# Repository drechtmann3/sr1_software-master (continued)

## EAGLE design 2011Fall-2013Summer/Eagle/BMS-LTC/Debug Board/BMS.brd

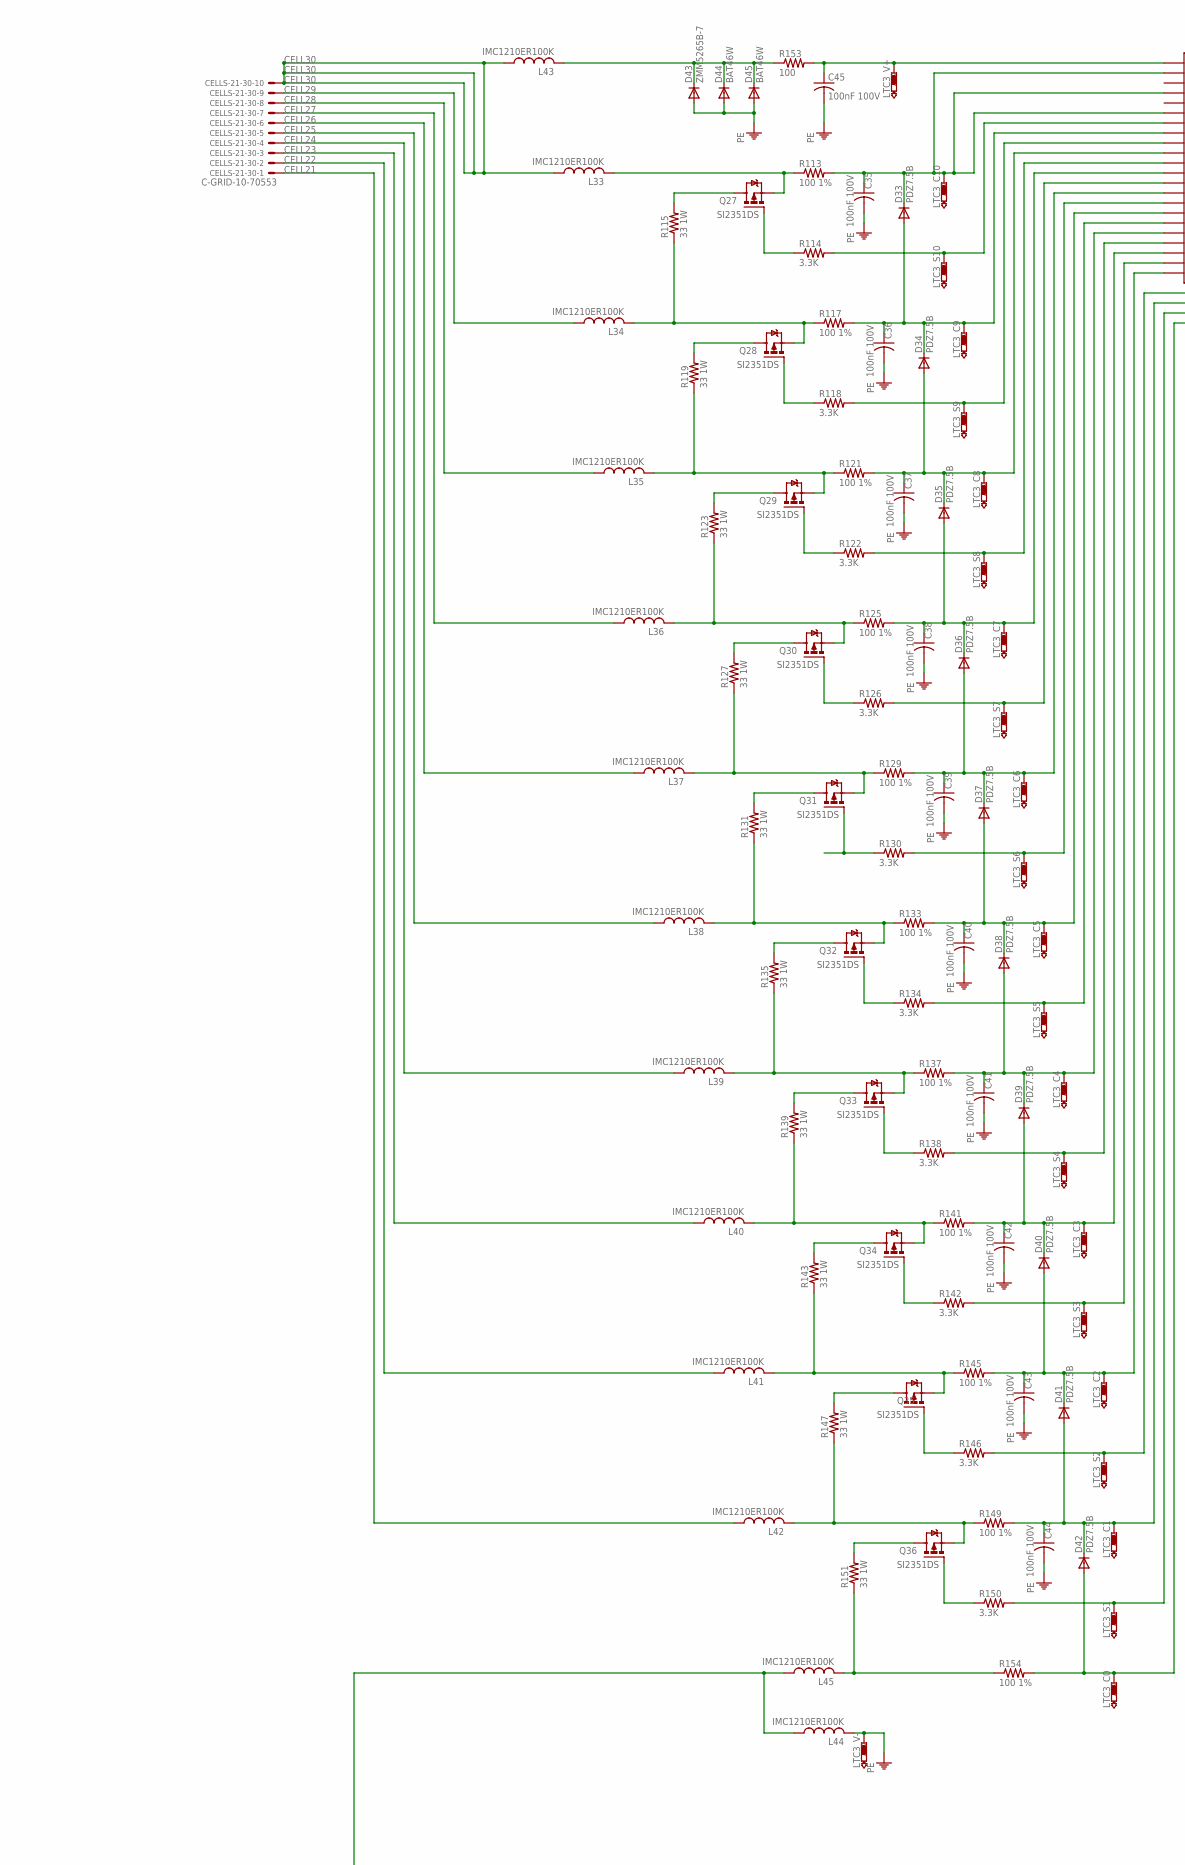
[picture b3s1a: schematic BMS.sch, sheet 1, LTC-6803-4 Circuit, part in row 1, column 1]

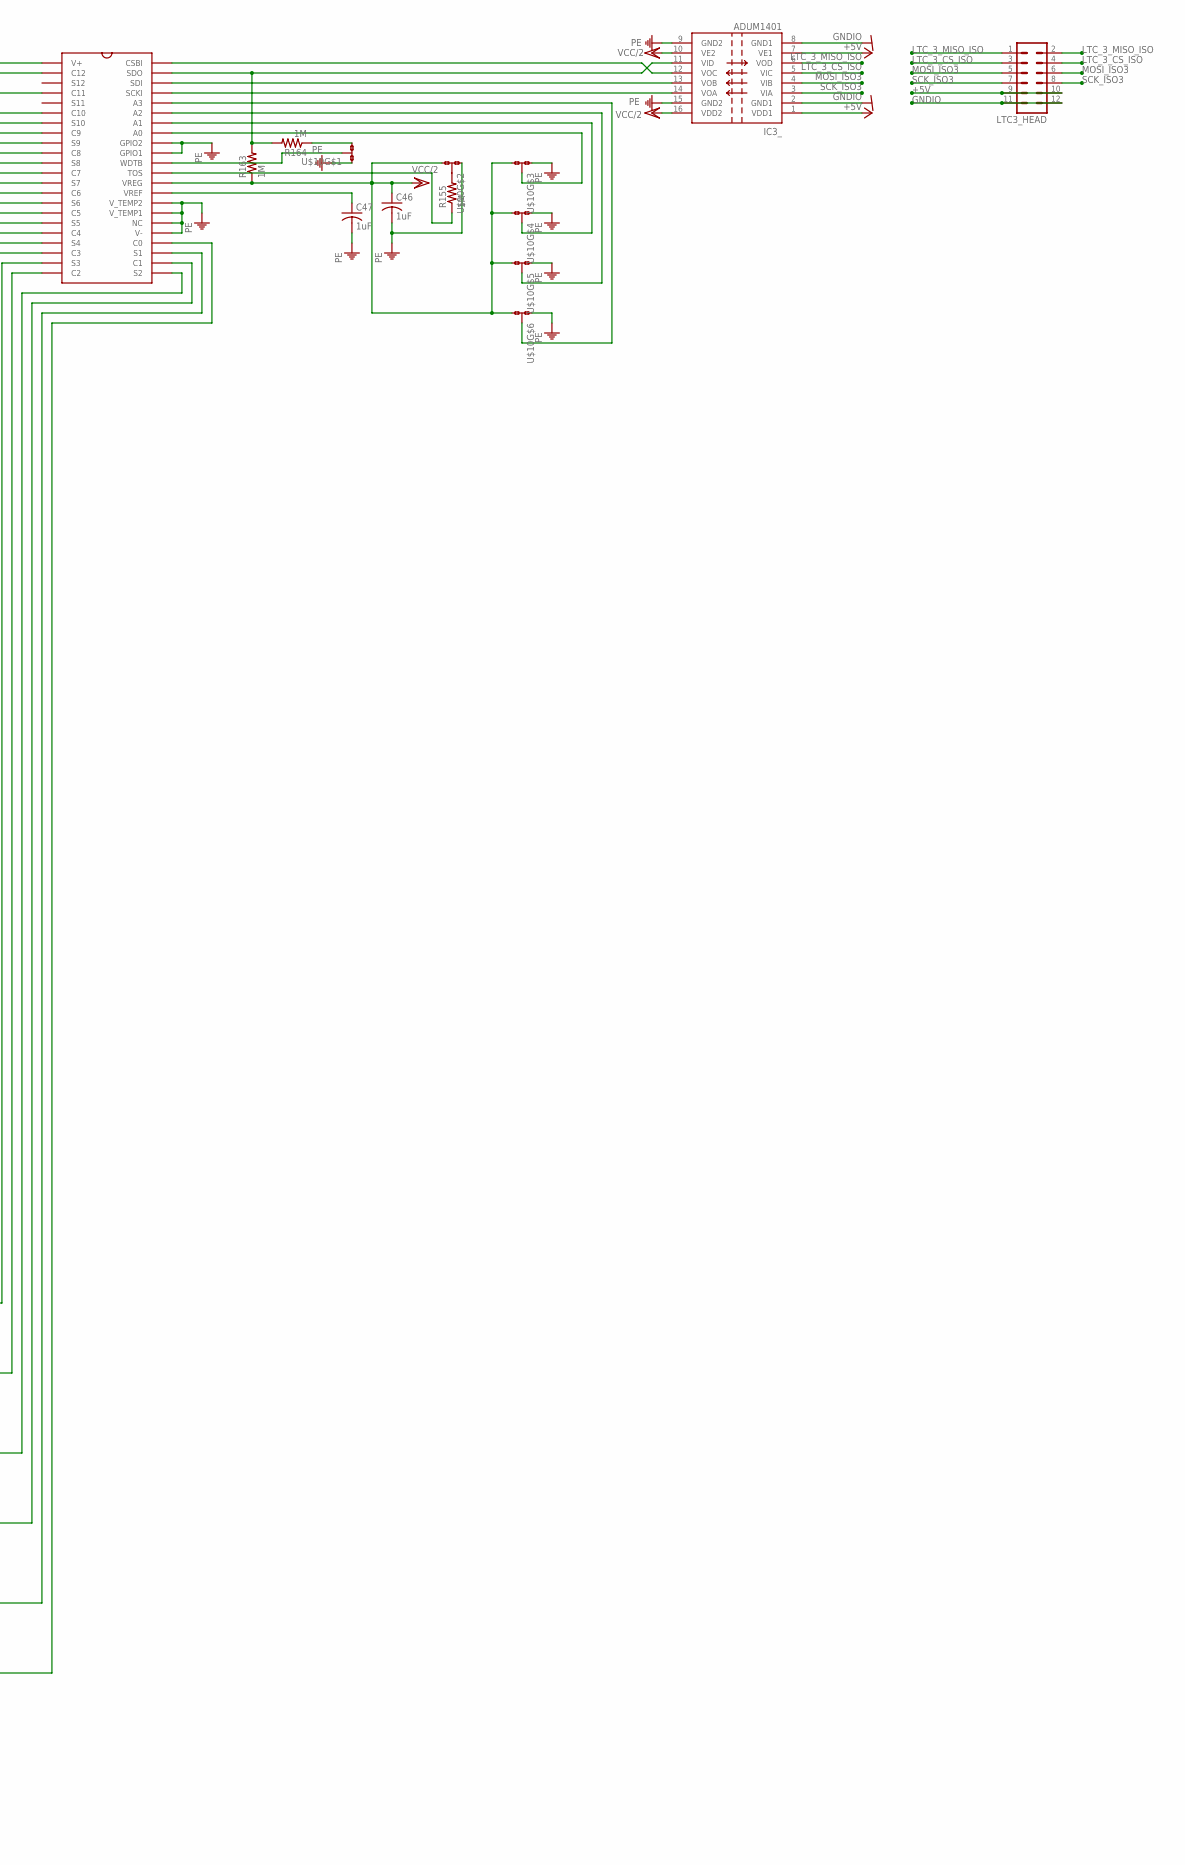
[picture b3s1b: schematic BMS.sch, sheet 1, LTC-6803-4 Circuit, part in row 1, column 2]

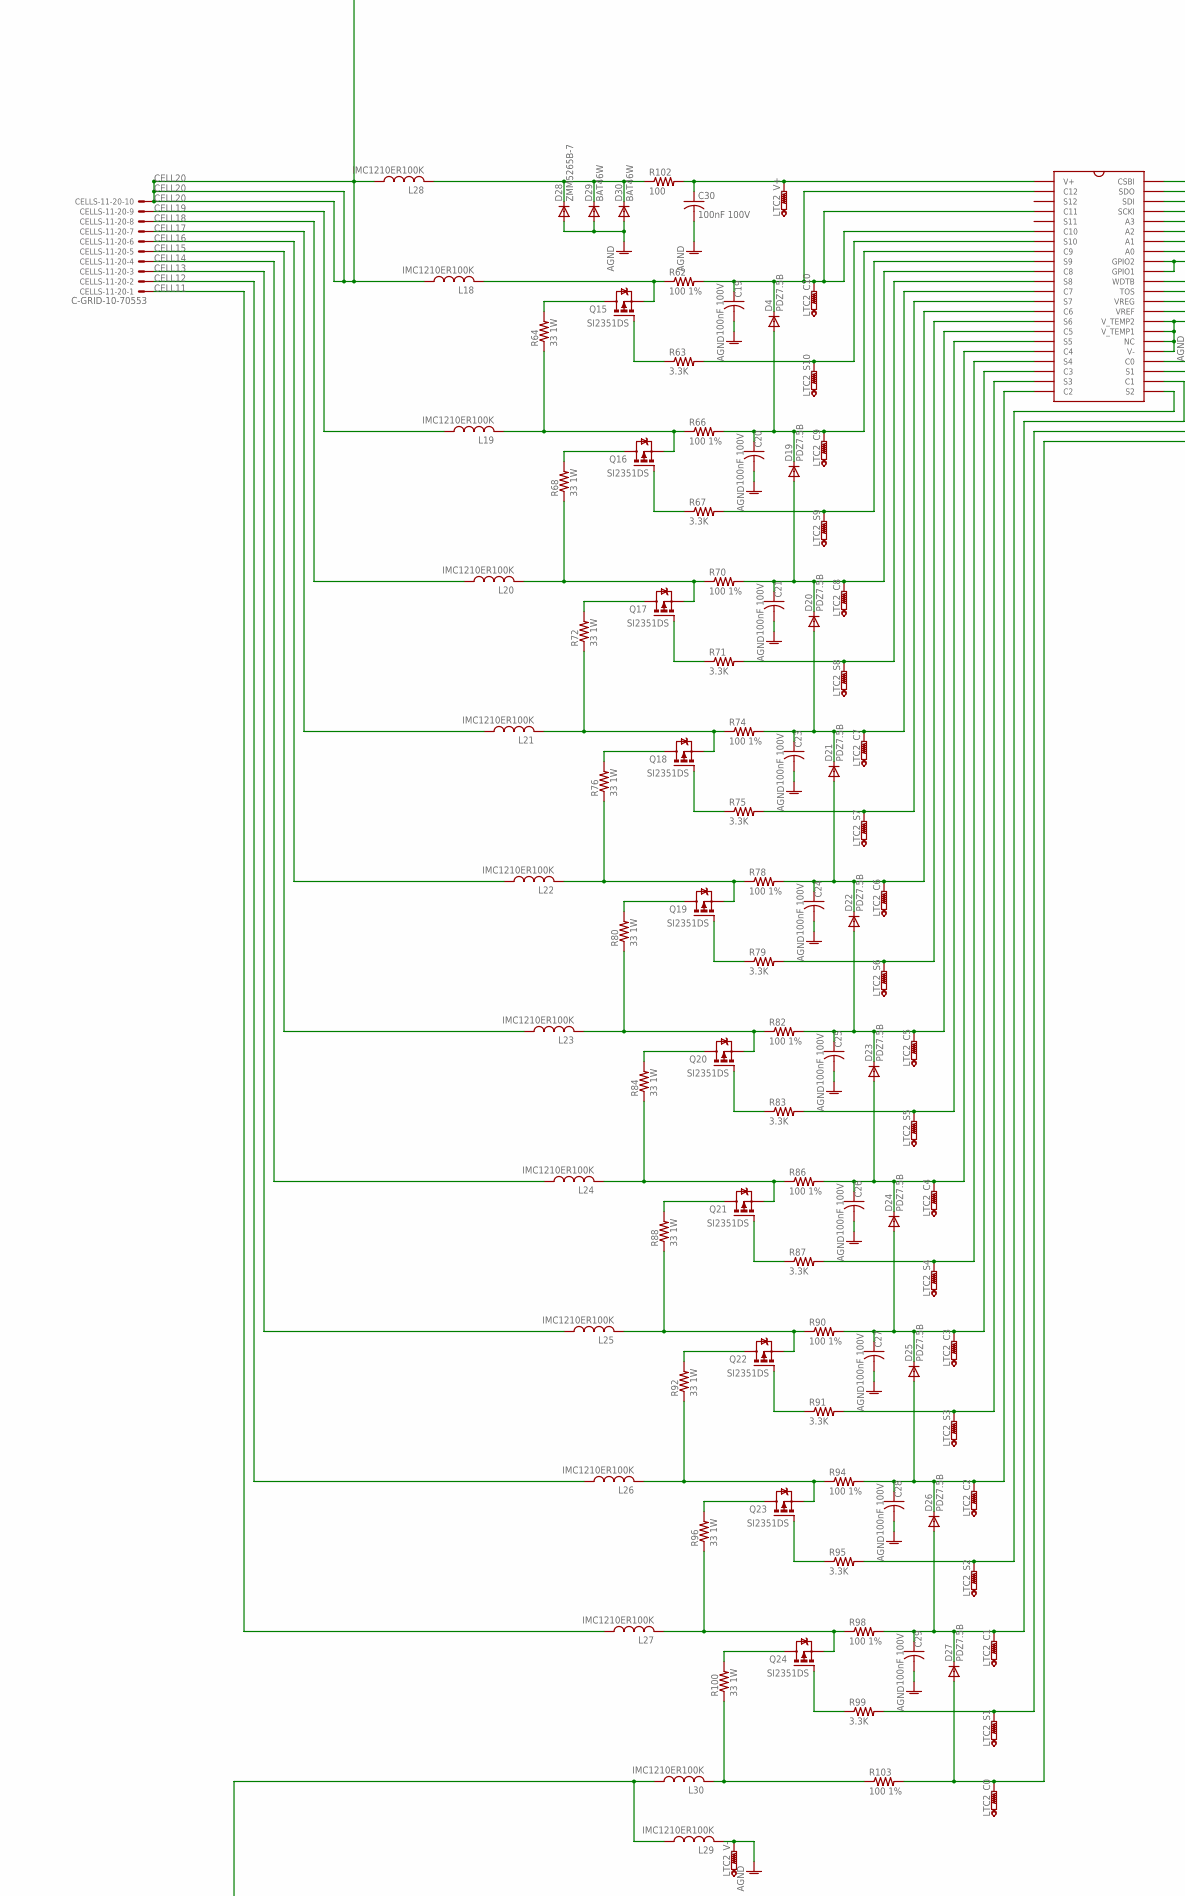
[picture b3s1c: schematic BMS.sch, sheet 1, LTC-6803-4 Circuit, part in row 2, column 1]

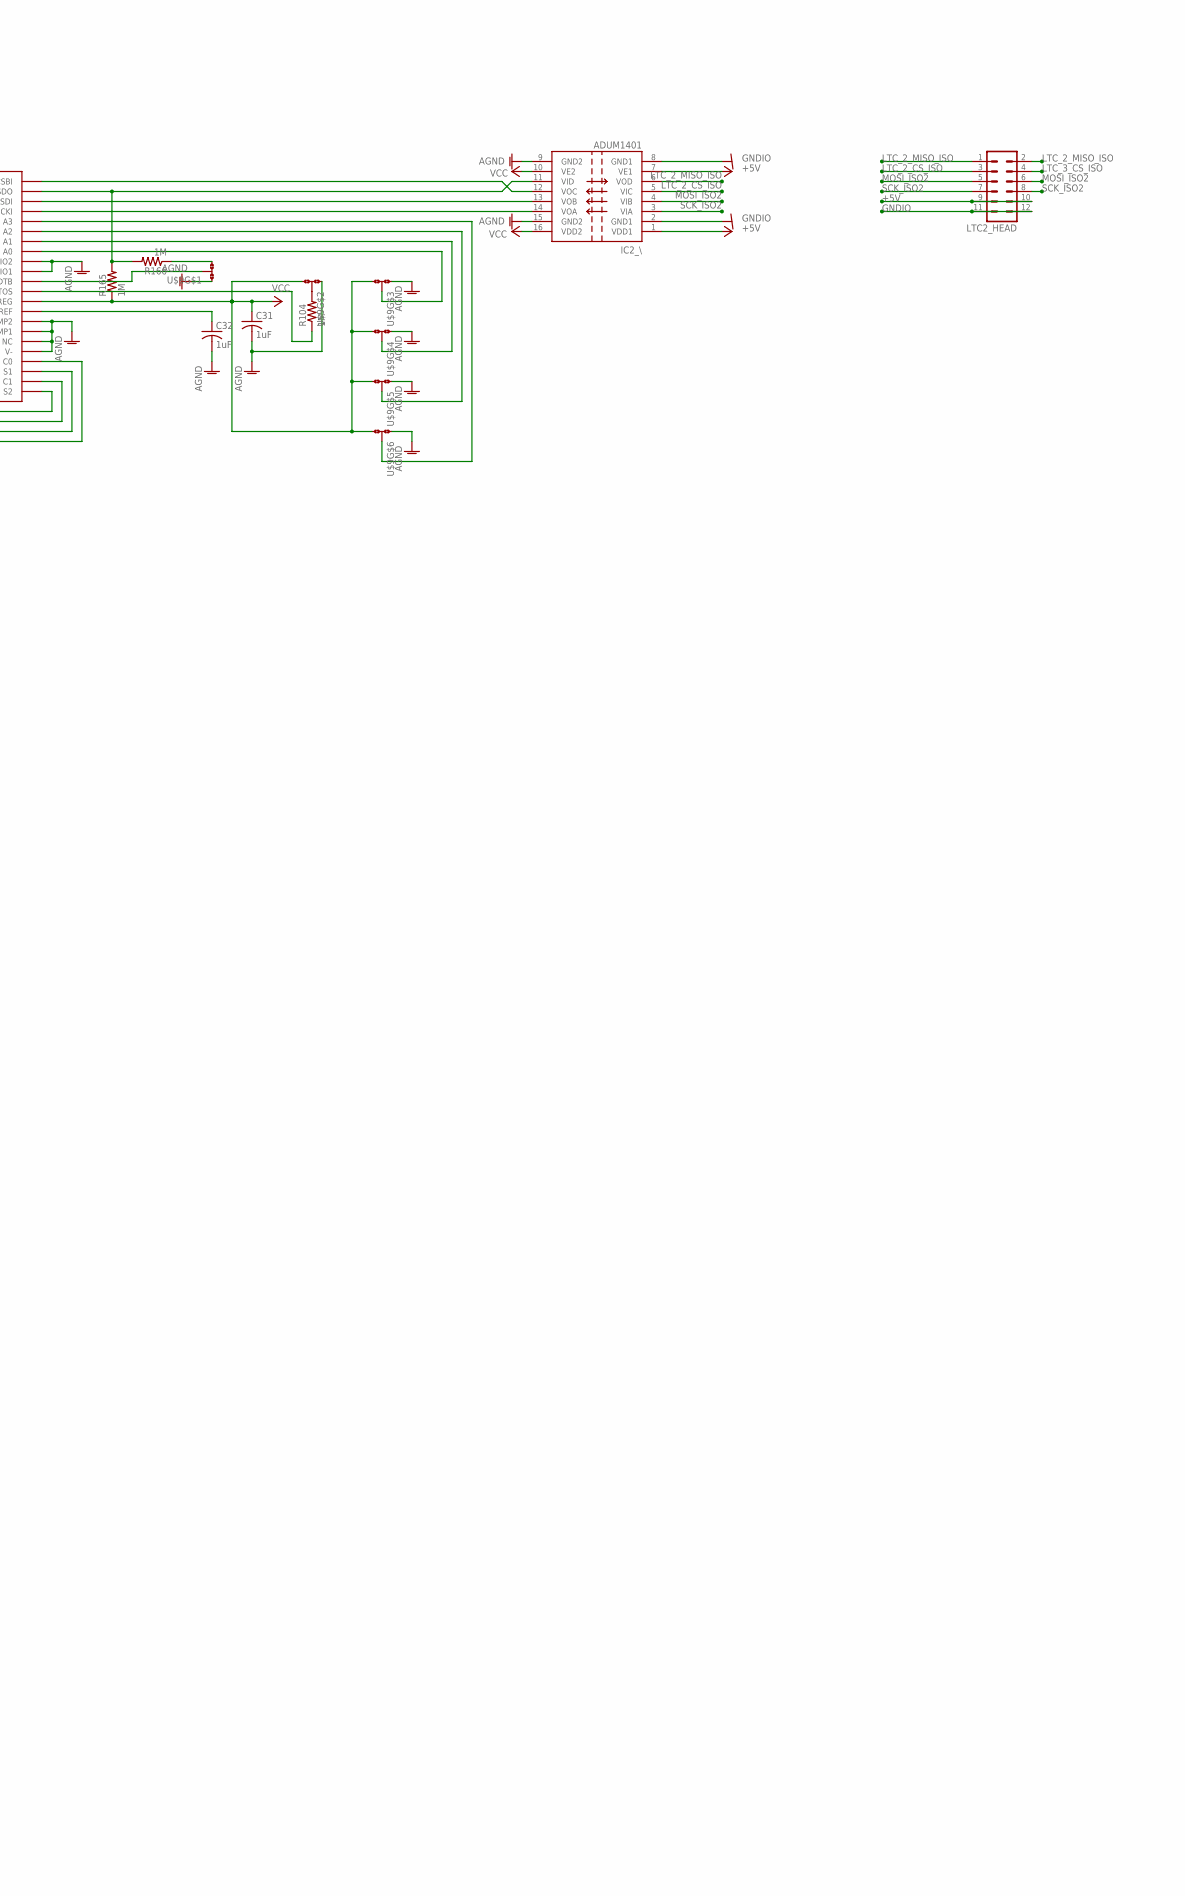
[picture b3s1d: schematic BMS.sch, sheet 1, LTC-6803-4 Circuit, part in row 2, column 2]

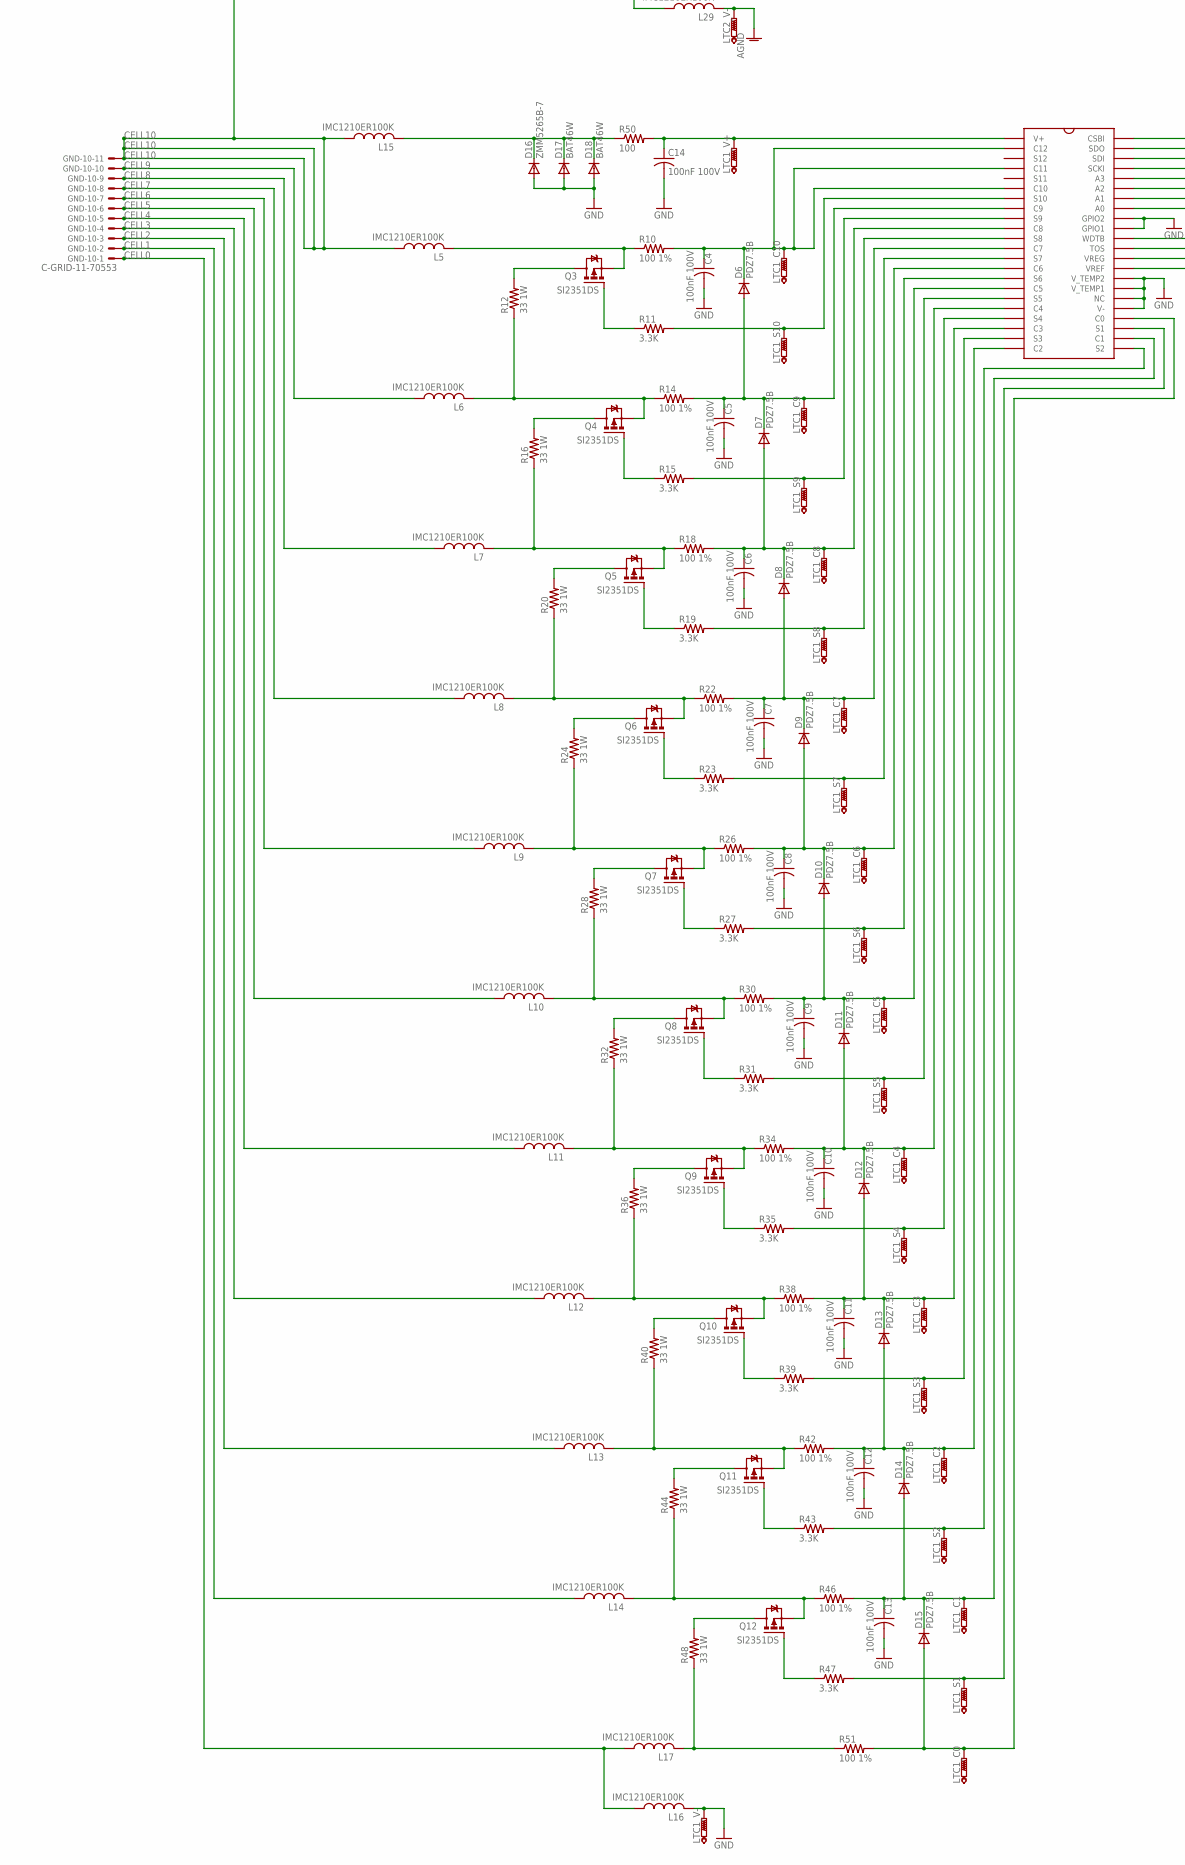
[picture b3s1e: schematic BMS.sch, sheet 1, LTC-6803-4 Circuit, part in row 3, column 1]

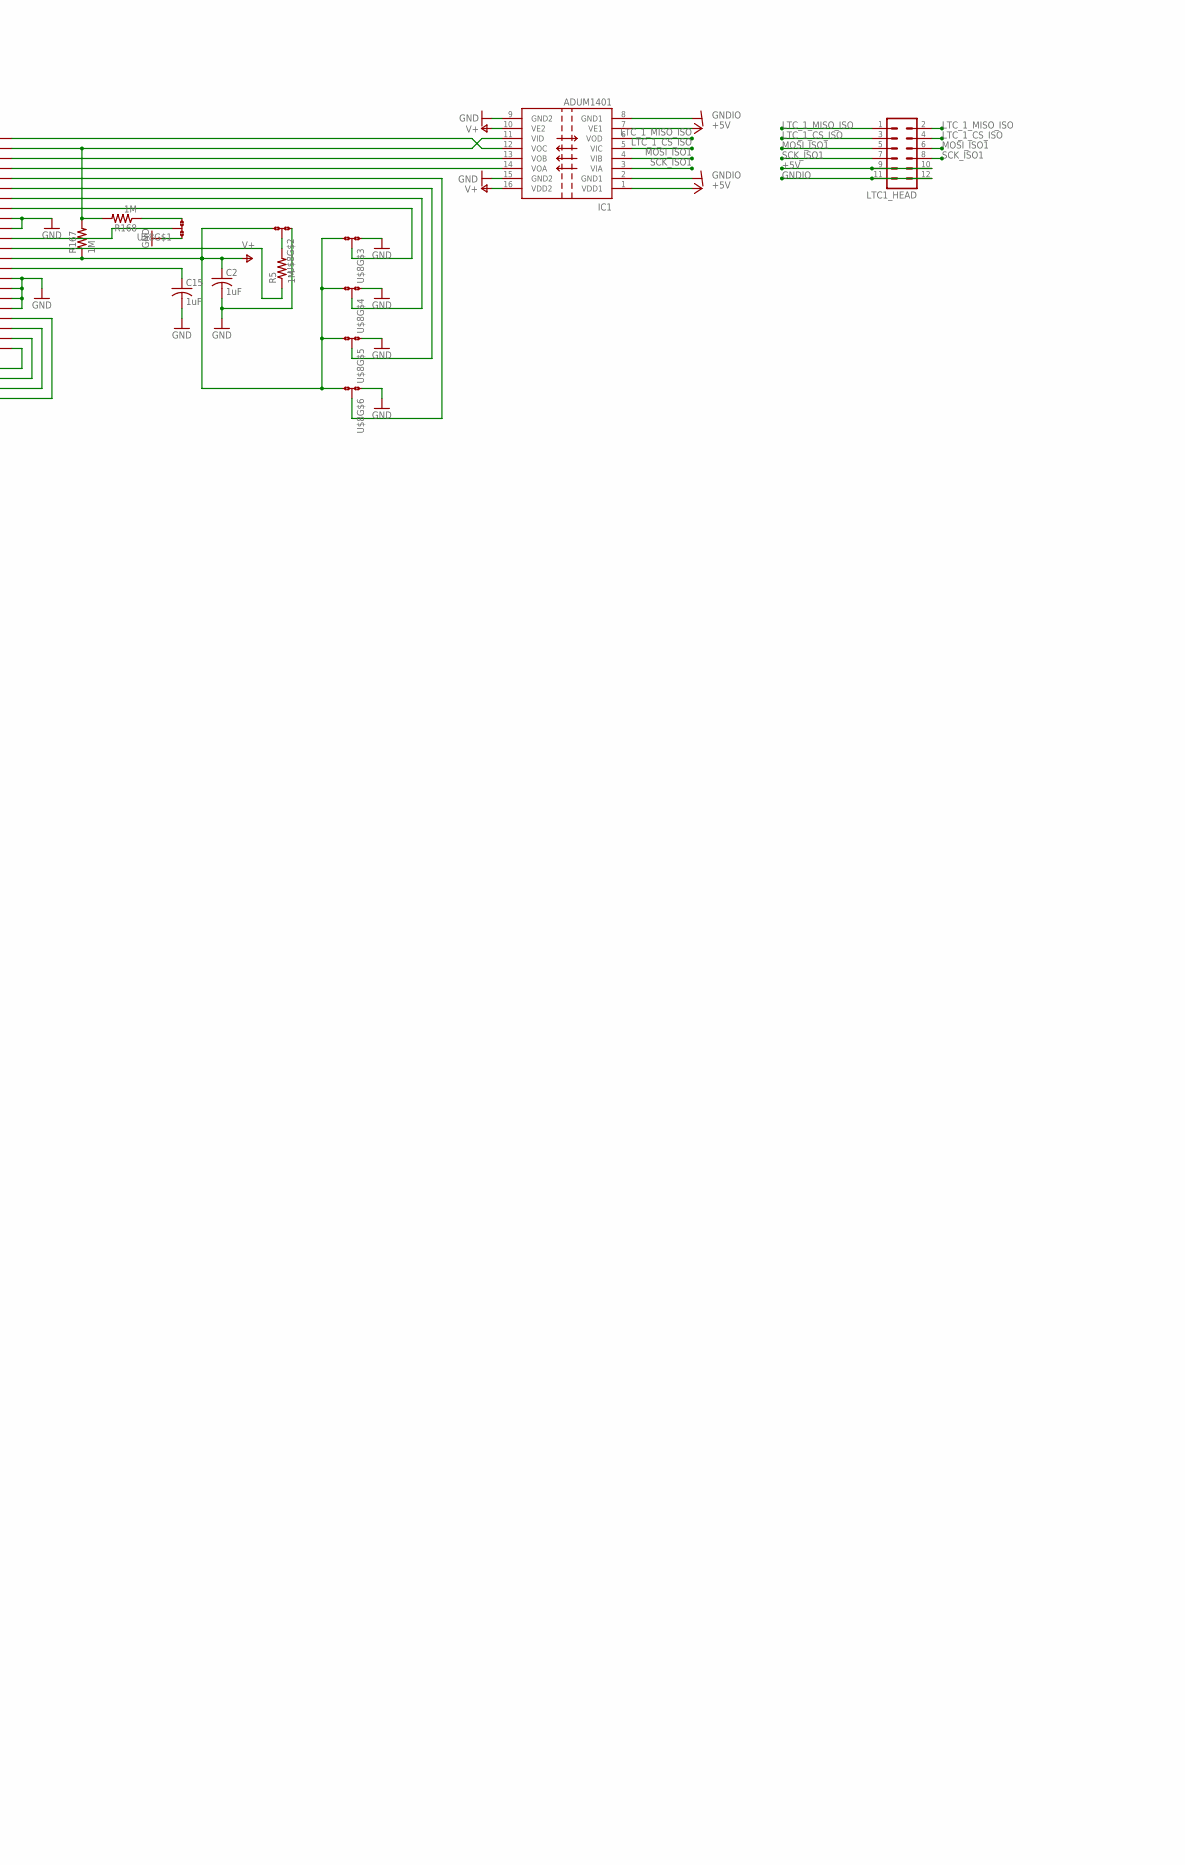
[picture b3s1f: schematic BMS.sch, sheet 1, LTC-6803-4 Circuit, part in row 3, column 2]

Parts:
C2, C15, C31, C32, C46, C47: 1uF; C1206
C4, C5, C6, C7, C8, C9, C10, C11, C12, C13, C14, C19, C20, C21, C23, C24, C25, C26, C27, C28, C29, C30, C35, C36, C37, C38, C39, C40, C41, C42, C43, C44, C45: 100nF 100V; C1206
CELLS-11-20, CELLS-21-30: C-GRID-10-70553; 70553-10
D4, D6, D7, D8, D9, D10, D11, D12, D13, D14, D15, D19, D20, D21, D22, D23, D24, D25, D26, D27, D33, D34, D35, D36, D37, D38, D39, D40, D41, D42: PDZ7.5B; SOD323-W
D16, D28, D43: ZMM5265B-7; MINIMELF
D17, D18, D29, D30, D44, D45: BAT46W; SOD123
GND-10: C-GRID-11-70553; 70553-11
IC1, IC2_\, IC3_: ADUM1401; SO16W
L5, L6, L7, L8, L9, L10, L11, L12, L13, L14, L15, L16, L17, L18, L19, L20, L21, L22, L23, L24, L25, L26, L27, L28, L29, L30, L33, L34, L35, L36, L37, L38, L39, L40, L41, L42, L43, L44, L45: IMC1210ER100K; L3225M
LTC1, LTC2, LTC3: LTC6803-4; SSOP44
LTC1_C0, LTC1_C1, LTC1_C2, LTC1_C3, LTC1_C4, LTC1_C5, LTC1_C6, LTC1_C7, LTC1_C8, LTC1_C9, LTC1_C10, LTC1_S1, LTC1_S2, LTC1_S3, LTC1_S4, LTC1_S5, LTC1_S6, LTC1_S7, LTC1_S8, LTC1_S9, LTC1_S10, LTC1_V+, LTC1_V-, LTC2_C0, LTC2_C1, LTC2_C2, LTC2_C3, LTC2_C4, LTC2_C5, LTC2_C6, LTC2_C7, LTC2_C8, LTC2_C9, LTC2_C10, LTC2_S1, LTC2_S2, LTC2_S3, LTC2_S4, LTC2_S5, LTC2_S6, LTC2_S7, LTC2_S8, LTC2_S9, LTC2_S10, LTC2_V+, LTC2_V-, LTC3_C0, LTC3_C1, LTC3_C2, LTC3_C3, LTC3_C4, LTC3_C5, LTC3_C6, LTC3_C7, LTC3_C8, LTC3_C9, LTC3_C10, LTC3_S1, LTC3_S2, LTC3_S3, LTC3_S4, LTC3_S5, LTC3_S6, LTC3_S7, LTC3_S8, LTC3_S9, LTC3_S10, LTC3_V+, LTC3_V-: TESTPAD-20MIL; 20MIL
LTC1_HEAD, LTC2_HEAD, LTC3_HEAD: MA06-2
Q3, Q4, Q5, Q6, Q7, Q8, Q9, Q10, Q11, Q12, Q15, Q16, Q17, Q18, Q19, Q20, Q21, Q22, Q23, Q24, Q27, Q28, Q29, Q30, Q31, Q32, Q33, Q34, Q35, Q36: SI2351DS; MICRO3
R5, R104, R155, R163, R164, R165, R166, R167, R168: 1M; R1206
R10, R14, R18, R22, R26, R30, R34, R38, R42, R46, R51, R62, R66, R70, R74, R78, R82, R86, R90, R94, R98, R103, R113, R117, R121, R125, R129, R133, R137, R141, R145, R149, R154: 100 1%; R1206
R11, R15, R19, R23, R27, R31, R35, R39, R43, R47, R63, R67, R71, R75, R79, R83, R87, R91, R95, R99, R114, R118, R122, R126, R130, R134, R138, R142, R146, R150: 3.3K; R1206
R12, R16, R20, R24, R28, R32, R36, R40, R44, R48, R64, R68, R72, R76, R80, R84, R88, R92, R96, R100, R115, R119, R123, R127, R131, R135, R139, R143, R147, R151: 33 1W; R2512
R50, R102, R153: 100; R1206
U$8, U$9, U$10: 3ROW_6POS

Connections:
+5V: IC1.1 (VDD1), IC1.7 (VE1), IC2_\.1 (VDD1), IC2_\.7 (VE1), IC3_.1 (VDD1), IC3_.7 (VE1), LTC1_HEAD.9, LTC1_HEAD.10, LTC2_HEAD.9, LTC2_HEAD.10, LTC3_HEAD.9, LTC3_HEAD.10; also elsewhere on the board
A0: LTC1.P$37 (A0), U$8.8 (2)
A1: LTC1.P$38 (A1), U$8.11 (2)
A2: LTC1.P$39 (A2), U$8.14 (2)
A3: LTC1.P$40 (A3), U$8.17 (2)
AGND: C19.2, C20.2, C21.2, C23.2, C24.2, C25.2, C26.2, C27.2, C28.2, C29.2, C30.2, C31.2, C32.2, D28.A, D29.A, D30.A, IC2_\.9 (GND2), IC2_\.15 (GND2), L29.2, LTC2.P$27 (V-), LTC2.P$28 (NC), LTC2.P$29 (V_TEMP1), LTC2.P$30 (V_TEMP2), LTC2.P$35 (GPIO1), LTC2.P$36 (GPIO2), LTC2_V-.P$1, U$9.1, U$9.4 (1), U$9.7 (1), U$9.10 (1), U$9.13 (1), U$9.16 (1)
CELL0: GND-10.1, L16.1, L17.1
CELL1: GND-10.2, L14.1
CELL2: GND-10.3, L13.1
CELL3: GND-10.4, L12.1
CELL4: GND-10.5, L11.1
CELL5: GND-10.6, L10.1
CELL6: GND-10.7, L9.1
CELL7: GND-10.8, L8.1
CELL8: GND-10.9, L7.1
CELL9: GND-10.10, L6.1
CELL10: GND-10.11, L5.1, L15.1, L29.1, L30.1
CELL11: CELLS-11-20.1, L27.1
CELL12: CELLS-11-20.2, L26.1
CELL13: CELLS-11-20.3, L25.1
CELL14: CELLS-11-20.4, L24.1
CELL15: CELLS-11-20.5, L23.1
CELL16: CELLS-11-20.6, L22.1
CELL17: CELLS-11-20.7, L21.1
CELL18: CELLS-11-20.8, L20.1
CELL19: CELLS-11-20.9, L19.1
CELL20: CELLS-11-20.10, L18.1, L28.1, L44.1, L45.1
CELL21: CELLS-21-30.1, L42.1
CELL22: CELLS-21-30.2, L41.1
CELL23: CELLS-21-30.3, L40.1
CELL24: CELLS-21-30.4, L39.1
CELL25: CELLS-21-30.5, L38.1
CELL26: CELLS-21-30.6, L37.1
CELL27: CELLS-21-30.7, L36.1
CELL28: CELLS-21-30.8, L35.1
CELL29: CELLS-21-30.9, L34.1
CELL30: CELLS-21-30.10, L33.1, L43.1
GND: C2.2, C4.2, C5.2, C6.2, C7.2, C8.2, C9.2, C10.2, C11.2, C12.2, C13.2, C14.2, C15.2, D16.A, D17.A, D18.A, IC1.9 (GND2), IC1.15 (GND2), L16.2, LTC1.P$27 (V-), LTC1.P$28 (NC), LTC1.P$29 (V_TEMP1), LTC1.P$30 (V_TEMP2), LTC1.P$35 (GPIO1), LTC1.P$36 (GPIO2), LTC1_V-.P$1, U$8.1, U$8.4 (1), U$8.7 (1), U$8.10 (1), U$8.13 (1), U$8.16 (1)
GNDIO: IC1.2 (GND1), IC1.8 (GND1), IC2_\.2 (GND1), IC2_\.8 (GND1), IC3_.2 (GND1), IC3_.8 (GND1), LTC1_HEAD.11, LTC1_HEAD.12, LTC2_HEAD.11, LTC2_HEAD.12, LTC3_HEAD.11, LTC3_HEAD.12; also elsewhere on the board
LTC_1_CS_ISO: IC1.5 (VIC), LTC1_HEAD.3, LTC1_HEAD.4
LTC_1_MISO_ISO: IC1.6 (VOD), LTC1_HEAD.1, LTC1_HEAD.2
LTC_2_CS_ISO: IC2_\.5 (VIC), LTC2_HEAD.3
LTC_2_MISO_ISO: IC2_\.6 (VOD), LTC2_HEAD.1, LTC2_HEAD.2
LTC_3_CS_ISO: IC3_.5 (VIC), LTC2_HEAD.4, LTC3_HEAD.3, LTC3_HEAD.4
LTC_3_MISO_ISO: IC3_.6 (VOD), LTC3_HEAD.1, LTC3_HEAD.2
MOSI_ISO1: IC1.4 (VIB), LTC1_HEAD.5, LTC1_HEAD.6
MOSI_ISO2: IC2_\.4 (VIB), LTC2_HEAD.5, LTC2_HEAD.6
MOSI_ISO3: IC3_.4 (VIB), LTC3_HEAD.5, LTC3_HEAD.6
unnamed: R104.2, U$9.5 (2)
unnamed: R155.2, U$10.5 (2)
unnamed: C4.1, D6.C, LTC1.P$2 (C12), LTC1.P$4 (C11), LTC1.P$6 (C10), LTC1_C10.P$1, R10.2
unnamed: R5.2, U$8.5 (2)
unnamed: L5.2, Q3.2 (S), R10.1
unnamed: IC1.12 (VOC), LTC1.P$44 (CSBI)
unnamed: IC1.13 (VOB), LTC1.P$42 (SDI)
unnamed: IC1.14 (VOA), LTC1.P$41 (SCKI)
unnamed: LTC1.P$7 (S10), LTC1_S10.P$1, R11.2
unnamed: Q3.1 (G), R11.1
unnamed: Q3.3 (D), R12.2
unnamed: L6.2, Q4.2 (S), R12.1, R14.1
unnamed: C15.1, LTC1.P$31 (VREF)
unnamed: C5.1, D6.A, D7.C, LTC1.P$8 (C9), LTC1_C9.P$1, R14.2
unnamed: LTC1.P$9 (S9), LTC1_S9.P$1, R15.2
unnamed: Q4.1 (G), R15.1
unnamed: Q4.3 (D), R16.2
unnamed: L7.2, Q5.2 (S), R16.1, R18.1
unnamed: C6.1, D7.A, D8.C, LTC1.P$10 (C8), LTC1_C8.P$1, R18.2
unnamed: LTC1.P$11 (S8), LTC1_S8.P$1, R19.2
unnamed: Q5.1 (G), R19.1
unnamed: Q5.3 (D), R20.2
unnamed: L8.2, Q6.2 (S), R20.1, R22.1
unnamed: C7.1, D8.A, D9.C, LTC1.P$12 (C7), LTC1_C7.P$1, R22.2
unnamed: LTC1.P$13 (S7), LTC1_S7.P$1, R23.2
unnamed: Q6.1 (G), R23.1
unnamed: Q6.3 (D), R24.2
unnamed: L9.2, Q7.2 (S), R24.1, R26.1
unnamed: C8.1, D9.A, D10.C, LTC1.P$14 (C6), LTC1_C6.P$1, R26.2
unnamed: C19.1, D4.C, LTC2.P$2 (C12), LTC2.P$4 (C11), LTC2.P$6 (C10), LTC2_C10.P$1, R62.2
unnamed: LTC1.P$15 (S6), LTC1_S6.P$1, R27.2
unnamed: Q7.1 (G), R27.1
unnamed: Q7.3 (D), R28.2
unnamed: L10.2, Q8.2 (S), R28.1, R30.1
unnamed: C9.1, D10.A, D11.C, LTC1.P$16 (C5), LTC1_C5.P$1, R30.2
unnamed: LTC1.P$17 (S5), LTC1_S5.P$1, R31.2
unnamed: Q8.1 (G), R31.1
unnamed: Q8.3 (D), R32.2
unnamed: L11.2, Q9.2 (S), R32.1, R34.1
unnamed: L18.2, Q15.2 (S), R62.1
unnamed: C10.1, D11.A, D12.C, LTC1.P$18 (C4), LTC1_C4.P$1, R34.2
unnamed: LTC2.P$7 (S10), LTC2_S10.P$1, R63.2
unnamed: LTC1.P$19 (S4), LTC1_S4.P$1, R35.2
unnamed: Q9.1 (G), R35.1
unnamed: Q9.3 (D), R36.2
unnamed: L12.2, Q10.2 (S), R36.1, R38.1
unnamed: Q15.1 (G), R63.1
unnamed: C11.1, D12.A, D13.C, LTC1.P$20 (C3), LTC1_C3.P$1, R38.2
unnamed: Q15.3 (D), R64.2
unnamed: LTC1.P$21 (S3), LTC1_S3.P$1, R39.2
unnamed: Q10.1 (G), R39.1
unnamed: Q10.3 (D), R40.2
unnamed: L13.2, Q11.2 (S), R40.1, R42.1
unnamed: L19.2, Q16.2 (S), R64.1, R66.1
unnamed: C12.1, D13.A, D14.C, LTC1.P$22 (C2), LTC1_C2.P$1, R42.2
unnamed: C20.1, D4.A, D19.C, LTC2.P$8 (C9), LTC2_C9.P$1, R66.2
unnamed: LTC2.P$9 (S9), LTC2_S9.P$1, R67.2
unnamed: LTC1.P$23 (S2), LTC1_S2.P$1, R43.2
unnamed: Q11.1 (G), R43.1
unnamed: Q11.3 (D), R44.2
unnamed: L14.2, Q12.2 (S), R44.1, R46.1
unnamed: Q16.1 (G), R67.1
unnamed: C13.1, D14.A, D15.C, LTC1.P$24 (C1), LTC1_C1.P$1, R46.2
unnamed: Q16.3 (D), R68.2
unnamed: LTC1.P$25 (S1), LTC1_S1.P$1, R47.2
unnamed: Q12.1 (G), R47.1
unnamed: Q12.3 (D), R48.2
unnamed: L17.2, R48.1, R51.1
unnamed: L20.2, Q17.2 (S), R68.1, R70.1
unnamed: D15.A, LTC1.P$26 (C0), LTC1_C0.P$1, R51.2
unnamed: C21.1, D19.A, D20.C, LTC2.P$10 (C8), LTC2_C8.P$1, R70.2
unnamed: D16.C, D17.C, D18.C, L15.2, R50.1
unnamed: C14.1, LTC1.P$1 (V+), LTC1_V+.P$1, R50.2
unnamed: LTC2.P$11 (S8), LTC2_S8.P$1, R71.2
unnamed: Q17.1 (G), R71.1
unnamed: Q17.3 (D), R72.2
unnamed: L21.2, Q18.2 (S), R72.1, R74.1
unnamed: C23.1, D20.A, D21.C, LTC2.P$12 (C7), LTC2_C7.P$1, R74.2
unnamed: LTC2.P$13 (S7), LTC2_S7.P$1, R75.2
unnamed: Q18.1 (G), R75.1
unnamed: Q18.3 (D), R76.2
unnamed: L22.2, Q19.2 (S), R76.1, R78.1
unnamed: C24.1, D21.A, D22.C, LTC2.P$14 (C6), LTC2_C6.P$1, R78.2
unnamed: LTC2.P$15 (S6), LTC2_S6.P$1, R79.2
unnamed: Q19.1 (G), R79.1
unnamed: Q19.3 (D), R80.2
unnamed: L23.2, Q20.2 (S), R80.1, R82.1
unnamed: C25.1, D22.A, D23.C, LTC2.P$16 (C5), LTC2_C5.P$1, R82.2
unnamed: LTC2.P$17 (S5), LTC2_S5.P$1, R83.2
unnamed: Q20.1 (G), R83.1
unnamed: Q20.3 (D), R84.2
unnamed: L24.2, Q21.2 (S), R84.1, R86.1
unnamed: C26.1, D23.A, D24.C, LTC2.P$18 (C4), LTC2_C4.P$1, R86.2
unnamed: LTC2.P$19 (S4), LTC2_S4.P$1, R87.2
unnamed: Q21.1 (G), R87.1
unnamed: Q21.3 (D), R88.2
unnamed: L25.2, Q22.2 (S), R88.1, R90.1
unnamed: C27.1, D24.A, D25.C, LTC2.P$20 (C3), LTC2_C3.P$1, R90.2
unnamed: LTC2.P$21 (S3), LTC2_S3.P$1, R91.2
unnamed: Q22.1 (G), R91.1
unnamed: Q22.3 (D), R92.2
unnamed: L26.2, Q23.2 (S), R92.1, R94.1
unnamed: C28.1, D25.A, D26.C, LTC2.P$22 (C2), LTC2_C2.P$1, R94.2
unnamed: LTC2.P$23 (S2), LTC2_S2.P$1, R95.2
unnamed: Q23.1 (G), R95.1
unnamed: Q23.3 (D), R96.2
unnamed: L27.2, Q24.2 (S), R96.1, R98.1
unnamed: C29.1, D26.A, D27.C, LTC2.P$24 (C1), LTC2_C1.P$1, R98.2
unnamed: LTC2.P$25 (S1), LTC2_S1.P$1, R99.2
unnamed: Q24.1 (G), R99.1
unnamed: Q24.3 (D), R100.2
unnamed: L30.2, R100.1, R103.1
unnamed: D27.A, LTC2.P$26 (C0), LTC2_C0.P$1, R103.2
unnamed: D28.C, D29.C, D30.C, L28.2, R102.1
unnamed: C30.1, LTC2.P$1 (V+), LTC2_V+.P$1, R102.2
unnamed: LTC2.P$33 (TOS), R104.1
unnamed: LTC2.P$39 (A2), U$9.14 (2)
unnamed: LTC2.P$40 (A3), U$9.17 (2)
unnamed: LTC2.P$38 (A1), U$9.11 (2)
unnamed: LTC2.P$37 (A0), U$9.8 (2)
unnamed: IC2_\.12 (VOC), LTC2.P$44 (CSBI)
unnamed: IC2_\.13 (VOB), LTC2.P$42 (SDI)
unnamed: IC2_\.14 (VOA), LTC2.P$41 (SCKI)
unnamed: C32.1, LTC2.P$31 (VREF)
unnamed: C35.1, D33.C, LTC3.P$2 (C12), LTC3.P$4 (C11), LTC3.P$6 (C10), LTC3_C10.P$1, R113.2
unnamed: L33.2, Q27.2 (S), R113.1
unnamed: LTC3.P$7 (S10), LTC3_S10.P$1, R114.2
unnamed: Q27.1 (G), R114.1
unnamed: Q27.3 (D), R115.2
unnamed: L34.2, Q28.2 (S), R115.1, R117.1
unnamed: C36.1, D33.A, D34.C, LTC3.P$8 (C9), LTC3_C9.P$1, R117.2
unnamed: LTC3.P$9 (S9), LTC3_S9.P$1, R118.2
unnamed: Q28.1 (G), R118.1
unnamed: Q28.3 (D), R119.2
unnamed: L35.2, Q29.2 (S), R119.1, R121.1
unnamed: C37.1, D34.A, D35.C, LTC3.P$10 (C8), LTC3_C8.P$1, R121.2
unnamed: LTC3.P$11 (S8), LTC3_S8.P$1, R122.2
unnamed: Q29.1 (G), R122.1
unnamed: Q29.3 (D), R123.2
unnamed: L36.2, Q30.2 (S), R123.1, R125.1
unnamed: C38.1, D35.A, D36.C, LTC3.P$12 (C7), LTC3_C7.P$1, R125.2
unnamed: LTC3.P$13 (S7), LTC3_S7.P$1, R126.2
unnamed: Q30.1 (G), R126.1
unnamed: Q30.3 (D), R127.2
unnamed: L37.2, Q31.2 (S), R127.1, R129.1
unnamed: C39.1, D36.A, D37.C, LTC3.P$14 (C6), LTC3_C6.P$1, R129.2
unnamed: LTC3.P$15 (S6), LTC3_S6.P$1, R130.2
unnamed: Q31.1 (G), R130.1
unnamed: Q31.3 (D), R131.2
unnamed: L38.2, Q32.2 (S), R131.1, R133.1
unnamed: C40.1, D37.A, D38.C, LTC3.P$16 (C5), LTC3_C5.P$1, R133.2
unnamed: LTC3.P$17 (S5), LTC3_S5.P$1, R134.2
unnamed: Q32.1 (G), R134.1
unnamed: Q32.3 (D), R135.2
unnamed: L39.2, Q33.2 (S), R135.1, R137.1
unnamed: C41.1, D38.A, D39.C, LTC3.P$18 (C4), LTC3_C4.P$1, R137.2
unnamed: LTC3.P$19 (S4), LTC3_S4.P$1, R138.2
unnamed: Q33.1 (G), R138.1
unnamed: Q33.3 (D), R139.2
unnamed: L40.2, Q34.2 (S), R139.1, R141.1
unnamed: C42.1, D39.A, D40.C, LTC3.P$20 (C3), LTC3_C3.P$1, R141.2
unnamed: LTC3.P$21 (S3), LTC3_S3.P$1, R142.2
unnamed: Q34.1 (G), R142.1
unnamed: Q34.3 (D), R143.2
unnamed: L41.2, Q35.2 (S), R143.1, R145.1
unnamed: C43.1, D40.A, D41.C, LTC3.P$22 (C2), LTC3_C2.P$1, R145.2
unnamed: LTC3.P$23 (S2), LTC3_S2.P$1, R146.2
unnamed: Q35.1 (G), R146.1
unnamed: Q35.3 (D), R147.2
unnamed: L42.2, Q36.2 (S), R147.1, R149.1
unnamed: C44.1, D41.A, D42.C, LTC3.P$24 (C1), LTC3_C1.P$1, R149.2
unnamed: LTC3.P$25 (S1), LTC3_S1.P$1, R150.2
unnamed: Q36.1 (G), R150.1
unnamed: Q36.3 (D), R151.2
unnamed: L45.2, R151.1, R154.1
unnamed: D42.A, LTC3.P$26 (C0), LTC3_C0.P$1, R154.2
unnamed: D43.C, D44.C, D45.C, L43.2, R153.1
unnamed: C45.1, LTC3.P$1 (V+), LTC3_V+.P$1, R153.2
unnamed: LTC3.P$33 (TOS), R155.1
unnamed: LTC3.P$39 (A2), U$10.14 (2)
unnamed: LTC3.P$40 (A3), U$10.17 (2)
unnamed: LTC3.P$38 (A1), U$10.11 (2)
unnamed: LTC3.P$37 (A0), U$10.8 (2)
unnamed: IC3_.12 (VOC), LTC3.P$44 (CSBI)
unnamed: IC3_.13 (VOB), LTC3.P$42 (SDI)
unnamed: IC3_.14 (VOA), LTC3.P$41 (SCKI)
unnamed: C47.1, LTC3.P$31 (VREF)
unnamed: IC1.11 (VID), LTC1.P$43 (SDO), R167.2, R168.2
unnamed: R168.1, U$8.3
unnamed: IC2_\.11 (VID), LTC2.P$43 (SDO), R165.2, R166.2
unnamed: R166.1, U$9.3
unnamed: LTC2.P$34 (WDTB), U$9.2
unnamed: LTC3.P$34 (WDTB), U$10.2
unnamed: IC3_.11 (VID), LTC3.P$43 (SDO), R163.2, R164.2
unnamed: R164.1, U$10.3
PE: C35.2, C36.2, C37.2, C38.2, C39.2, C40.2, C41.2, C42.2, C43.2, C44.2, C45.2, C46.2, C47.2, D43.A, D44.A, D45.A, IC3_.9 (GND2), IC3_.15 (GND2), L44.2, LTC3.P$27 (V-), LTC3.P$28 (NC), LTC3.P$29 (V_TEMP1), LTC3.P$30 (V_TEMP2), LTC3.P$35 (GPIO1), LTC3.P$36 (GPIO2), LTC3_V-.P$1, U$10.1, U$10.4 (1), U$10.7 (1), U$10.10 (1), U$10.13 (1), U$10.16 (1)
SCK_ISO1: IC1.3 (VIA), LTC1_HEAD.7, LTC1_HEAD.8
SCK_ISO2: IC2_\.3 (VIA), LTC2_HEAD.7, LTC2_HEAD.8
SCK_ISO3: IC3_.3 (VIA), LTC3_HEAD.7, LTC3_HEAD.8
TOS: LTC1.P$33 (TOS), R5.1
V+: C2.1, IC1.10 (VE2), IC1.16 (VDD2), LTC1.P$32 (VREG), R167.1, U$8.6 (3), U$8.9 (3), U$8.12 (3), U$8.15 (3), U$8.18 (3)
VCC: C31.1, IC2_\.10 (VE2), IC2_\.16 (VDD2), LTC2.P$32 (VREG), R165.1, U$9.6 (3), U$9.9 (3), U$9.12 (3), U$9.15 (3), U$9.18 (3)
VCC/2: C46.1, IC3_.10 (VE2), IC3_.16 (VDD2), LTC3.P$32 (VREG), R163.1, U$10.6 (3), U$10.9 (3), U$10.12 (3), U$10.15 (3), U$10.18 (3)
WDTB: LTC1.P$34 (WDTB), U$8.2

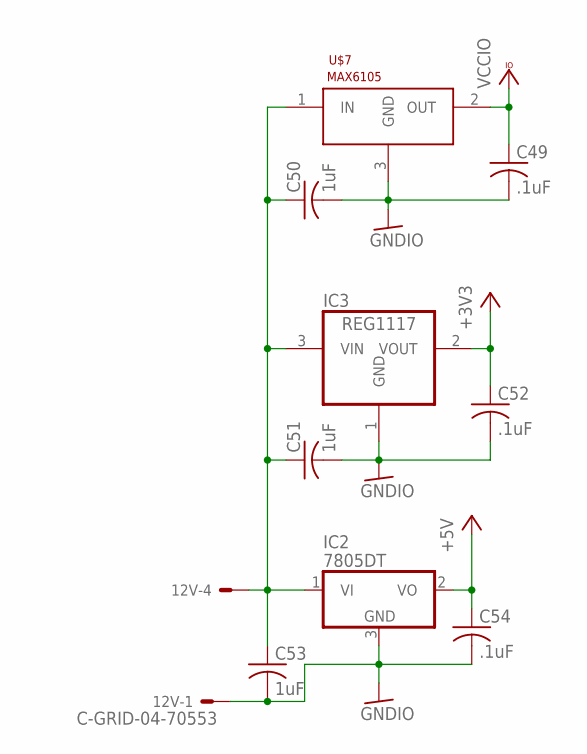
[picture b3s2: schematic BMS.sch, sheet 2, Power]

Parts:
12V: C-GRID-04-70553; 70553-04
C49, C52, C54: .1uF; C1206
C50, C51, C53: 1uF; C1206
IC2: 7805DT; TO252
IC3: REG1117; SOT223
U$7: MAX6105; SOT23

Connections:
12V: 12V.4, C50.1, C51.1, C53.1, IC2.1 (VI), IC3.3 (VIN), U$7.1 (IN); also elsewhere on the board
+3V3: C52.1, IC3.2 (VOUT); also elsewhere on the board
+5V: C54.1, IC2.2 (VO); also elsewhere on the board
GNDIO: 12V.1, C49.2, C50.2, C51.2, C52.2, C53.2, C54.2, IC2.3 (GND), IC3.1 (GND), U$7.3 (GND); also elsewhere on the board
VCCIO: C49.1, U$7.2 (OUT); also elsewhere on the board

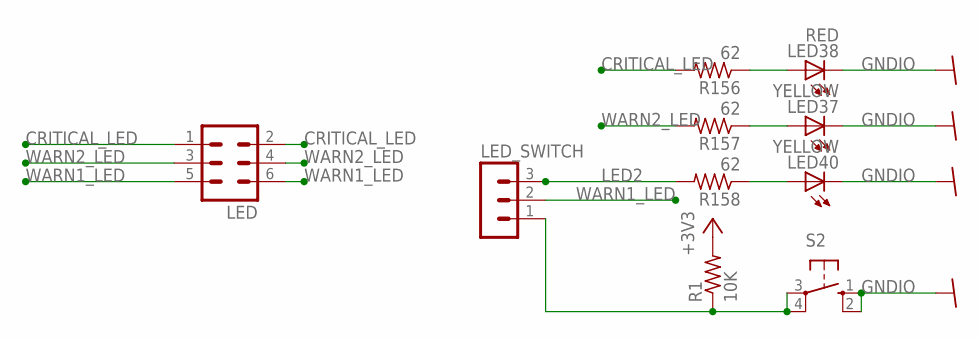
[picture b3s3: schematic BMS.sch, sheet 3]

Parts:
LED: MA03-2
LED37, LED40: YELLOW; CHIPLED_1206
LED38: RED; CHIPLED_1206
LED_SWITCH: MA03-1
R1: 10K; R1206
R156, R157, R158: 62; R1206
S2: 10-XX; B3F-10XX

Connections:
+3V3: R1.2; also elsewhere on the board
CRITICAL_LED: LED.1, LED.2, R156.2
GNDIO: LED37.C, LED38.C, LED40.C, S2.1 (S), S2.2 (S1); also elsewhere on the board
LED2: LED_SWITCH.3, R158.2
unnamed: LED_SWITCH.1, R1.1, S2.3, S2.4 (P1)
unnamed: LED37.A, R157.1
unnamed: LED38.A, R156.1
unnamed: LED40.A, R158.1
WARN1_LED: LED.5, LED.6, LED_SWITCH.2
WARN2_LED: LED.3, LED.4, R157.2

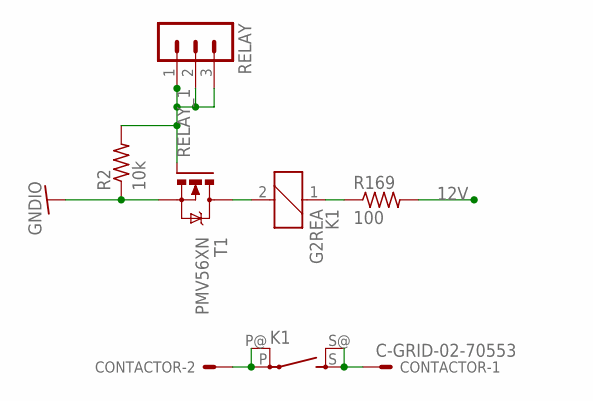
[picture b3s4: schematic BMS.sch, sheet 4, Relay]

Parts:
CONTACTOR: C-GRID-02-70553; 70553-02
K1: G2REA
R2: 10k; R1206
R169: 100; R1206
RELAY: MA03-1
T1: PMV56XN; SOT23

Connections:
12V: R169.2; also elsewhere on the board
GNDIO: R2.1, T1.2 (S); also elsewhere on the board
unnamed: K1.2, T1.3 (D)
unnamed: K1.1, R169.1
unnamed: CONTACTOR.2, K1.P, K1.P@
unnamed: CONTACTOR.1, K1.S, K1.S@ (S)
RELAY_1: R2.2, RELAY.1, RELAY.2, RELAY.3, T1.1 (G)
